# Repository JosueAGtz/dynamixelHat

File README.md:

# RaspberryPi Dynamixel Hat

The Raspberry Pi Zero Dynamixel Hat it's an easy to use hardware that allows you to connect and communicate with Dynamixel Servo Motors by using the Savage Electronics AX interface circuit, providing the half-duplex communication needed by these motors, its implemented in it a voltage converter for all the signals to the Raspberry allowing a secure communication in terms of logical levels.

It also implements a MAX25232ATCG/V+ which is a synchronous step-down DC-DC converter optimized for applications with high power density, This regulator will let you power your Raspberry directly from a battery and also provide power to your motors.

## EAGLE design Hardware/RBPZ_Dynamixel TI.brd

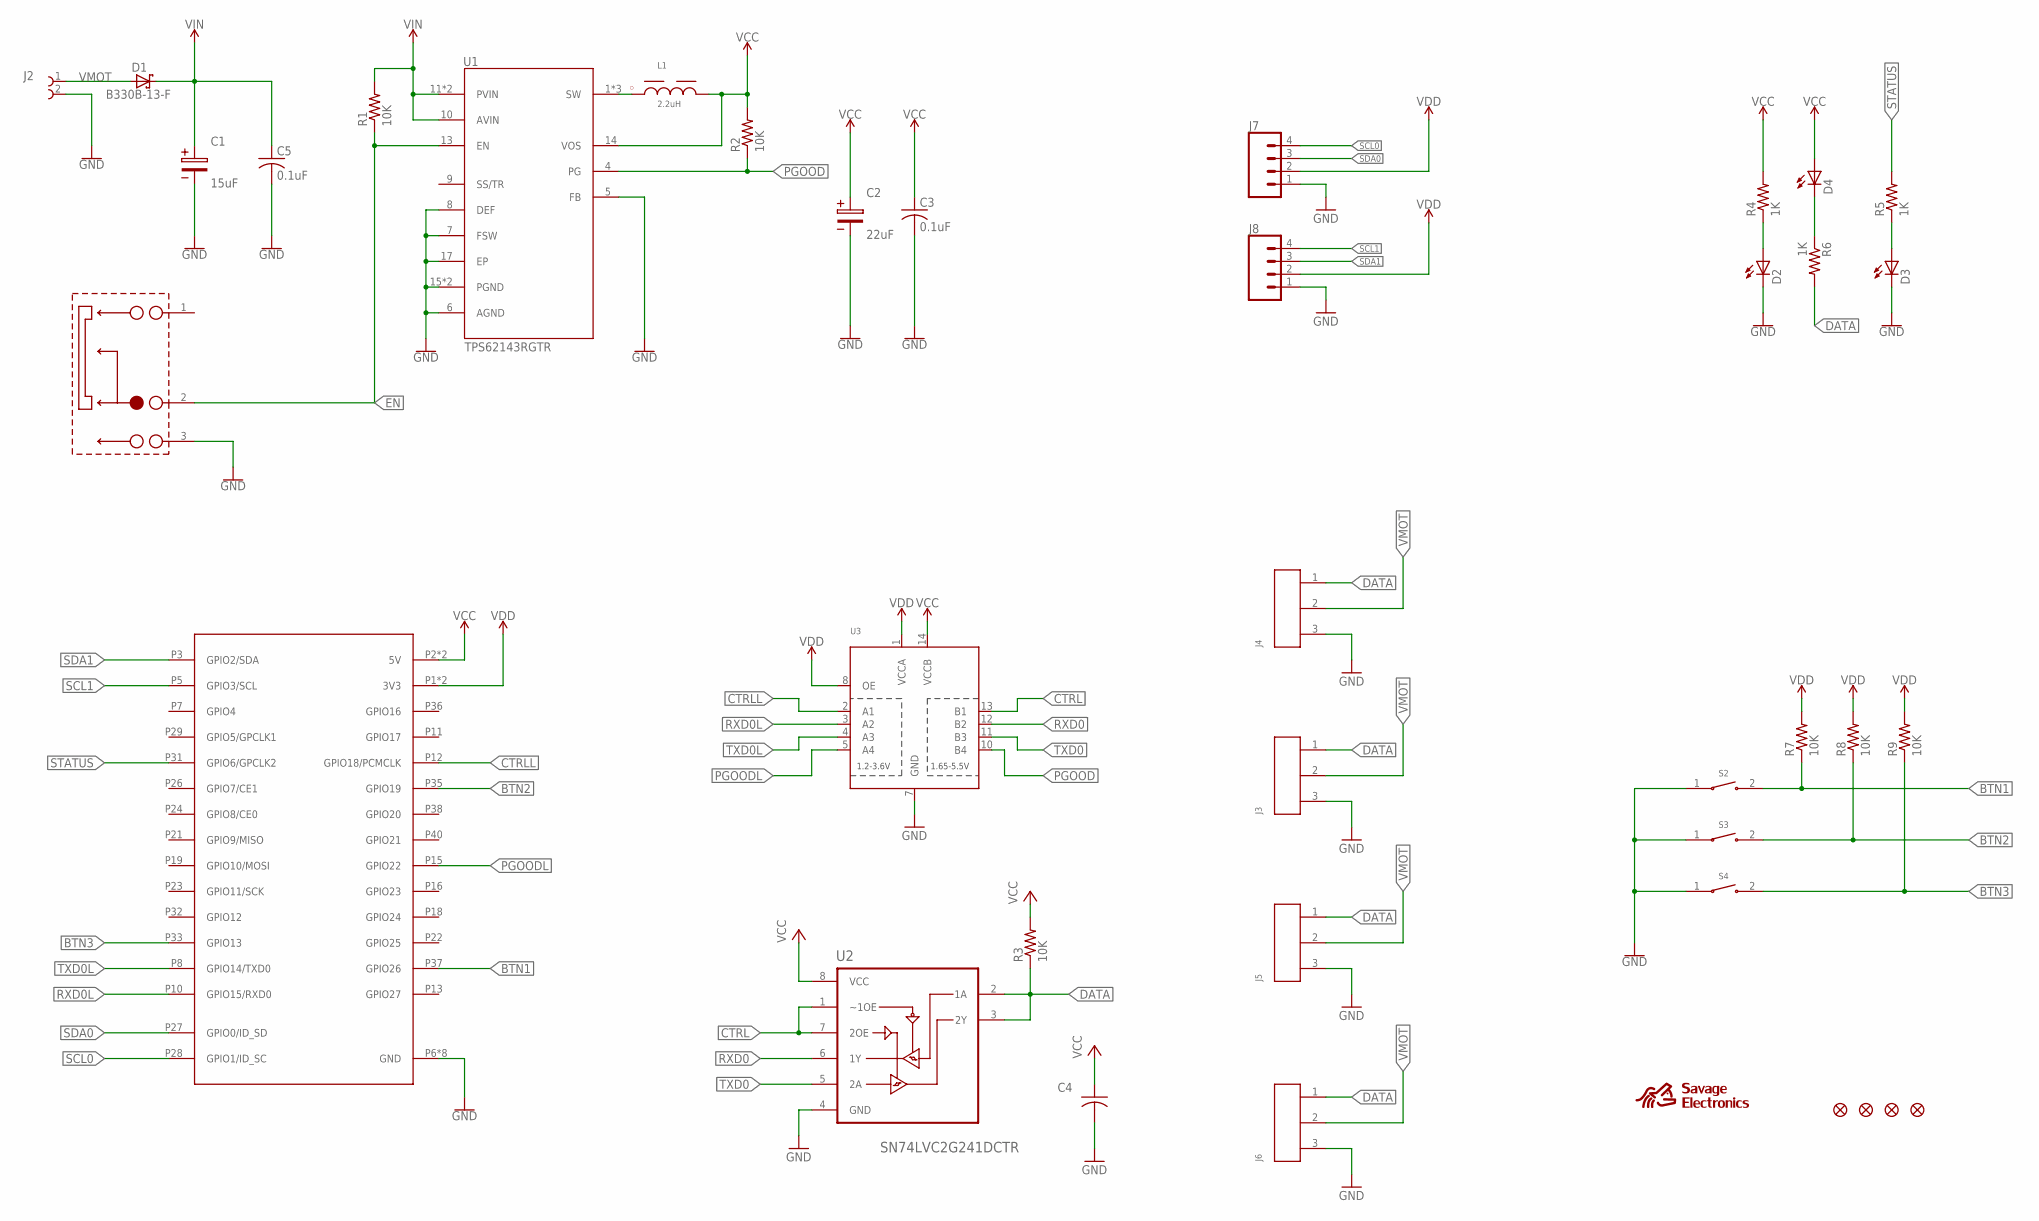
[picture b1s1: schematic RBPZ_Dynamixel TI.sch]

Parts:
C1: 15uF; 3.5X1.6X2.1(BXCXA)
C2: 22uF; 3.5X1.6X2.1(BXCXA)
C3, C5: 0.1uF; C0805
C4: 1uF; C0805
D1: B330B-13-F; DIONM4336X250N
D2, D3, D4: LEDCHIP-LED0805; CHIP-LED0805
FID1, FID2, FID3, FID4: FIDUCIAL""; FIDUCIAL_1MM
J1: RBPZERO; 61004021821_RASPBERRYPIZERO
J2: 691137910002
J3, J4, J5, J6: 64600311622
J7, J8: CONN_04SMD2; 1X04_1MM_RA
L1: 2.2uH; WE-LQFS_48X8
R1, R2, R3, R7, R8, R9: 10K; R0805
R4, R5, R6: 1K; R0805
S1: 450404015514
S2, S3, S4: 434123025826-2PIN
U1: TPS62143RGTR; QFN50P300X300X80-17N
U2: SN74LVC2G241DCTR; SOP65P400X130-8N
U3: TXB0104PWR; TSSOP14

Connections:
BTN1: J1.P37 (GPIO26), R7.1, S2.2
BTN2: J1.P35 (GPIO19), R8.1, S3.2
BTN3: J1.P33 (GPIO13), R9.1, S4.2
CTRL: U2.1 (~1OE), U2.7 (2OE), U3.13 (B1)
CTRLL: J1.P12 (GPIO18/PCMCLK), U3.2 (A1)
DATA: J3.1, J4.1, J5.1, J6.1, R3.1, R6.2, U2.2 (1A), U2.3 (2Y)
EN: R1.1, S1.2, U1.13 (EN)
GND: C1.2, C2.2, C3.2, C4.2, C5.2, D2.C, D3.C, J1.P6 (GND), J1.P9 (GND), J1.P14 (GND), J1.P20 (GND), J1.P25 (GND), J1.P30 (GND), J1.P34 (GND), J1.P39 (GND), J2.2, J3.3, J4.3, J5.3, J6.3, J7.1, J8.1, S1.3, S2.1, S3.1, S4.1, U1.5 (FB), U1.6 (AGND), U1.7 (FSW), U1.8 (DEF), U1.15 (PGND), U1.16 (PGND), U1.17 (EP), U2.4 (GND), U3.7 (GND)
unnamed: D4.C, R6.1
unnamed: D2.A, R4.1
unnamed: L1.1, U1.1 (SW), U1.2 (SW), U1.3 (SW)
unnamed: D3.A, R5.1
PGOOD: R2.1, U1.4 (PG), U3.10 (B4)
PGOODL: J1.P15 (GPIO22), U3.5 (A4)
RXD0: U2.6 (1Y), U3.12 (B2)
RXD0L: J1.P10 (GPIO15/RXD0), U3.3 (A2)
SCL0: J1.P28 (GPIO1/ID_SC), J7.4
SCL1: J1.P5 (GPIO3/SCL), J8.4
SDA0: J1.P27 (GPIO0/ID_SD), J7.3
SDA1: J1.P3 (GPIO2/SDA), J8.3
STATUS: J1.P31 (GPIO6/GPCLK2), R5.2
TXD0: U2.5 (2A), U3.11 (B3)
TXD0L: J1.P8 (GPIO14/TXD0), U3.4 (A3)
VCC: C2.1, C3.1, C4.1, D4.A, J1.P2 (5V), J1.P4 (5V), L1.2, R2.2, R3.2, R4.2, U1.14 (VOS), U2.8 (VCC), U3.14 (VCCB)
VDD: J1.P1 (3V3), J1.P17 (3V3), J7.2, J8.2, R7.2, R8.2, R9.2, U3.1 (VCCA), U3.8 (OE)
VIN: C1.1, C5.1, D1.1 (C), R1.2, U1.10 (AVIN), U1.11 (PVIN), U1.12 (PVIN)
VMOT: D1.2 (A), J2.1, J3.2, J4.2, J5.2, J6.2

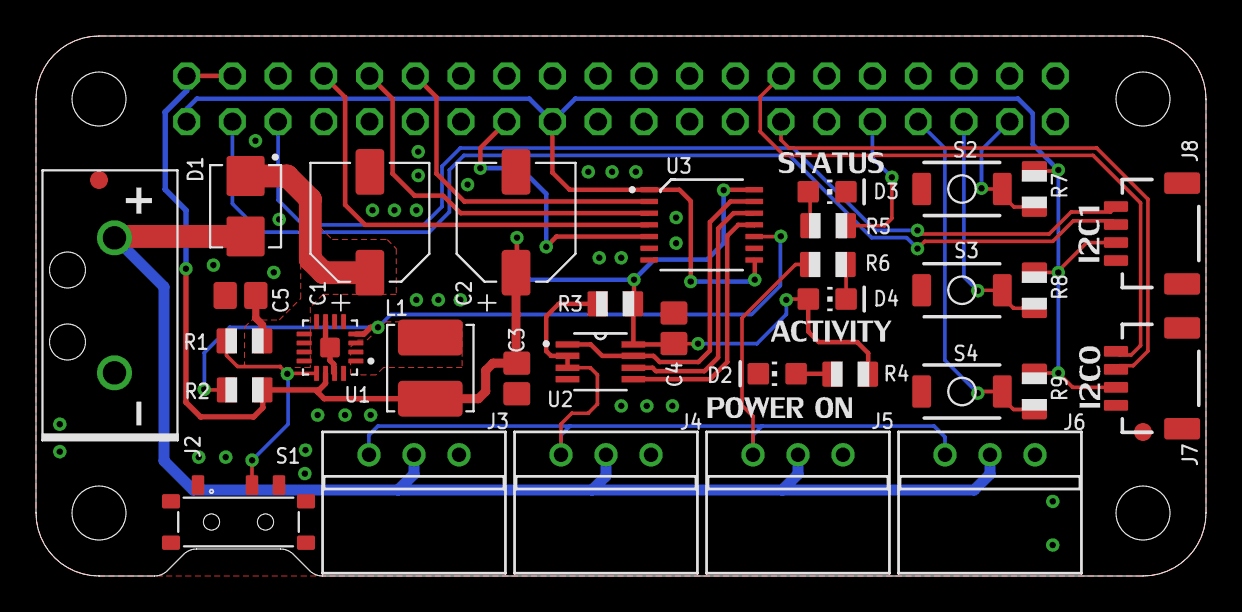
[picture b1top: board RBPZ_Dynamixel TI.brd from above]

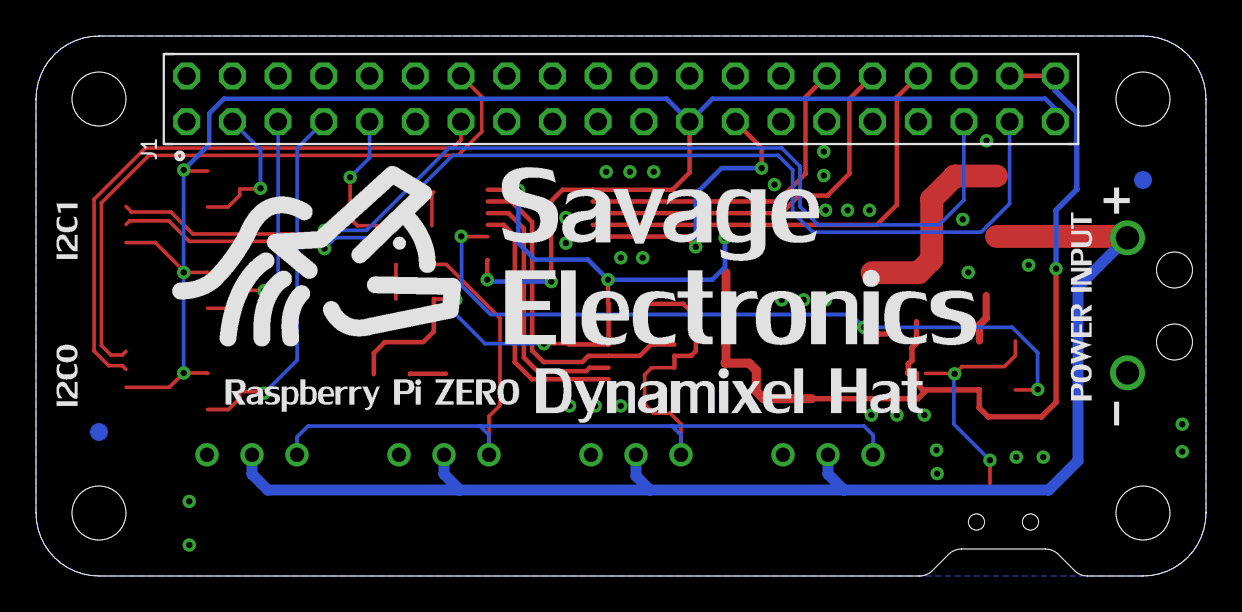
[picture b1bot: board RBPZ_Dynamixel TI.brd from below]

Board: 2 copper layers, 65.0 x 30.0 mm, 38 parts (3 on the bottom side), 27 nets.

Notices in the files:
parts and their libraries:
microbuilder: This work is placed in the public domain, and may be freely used for commercial and non-commercial work with the following conditions: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
Capacitors: Copyright: Würth Elektronik
